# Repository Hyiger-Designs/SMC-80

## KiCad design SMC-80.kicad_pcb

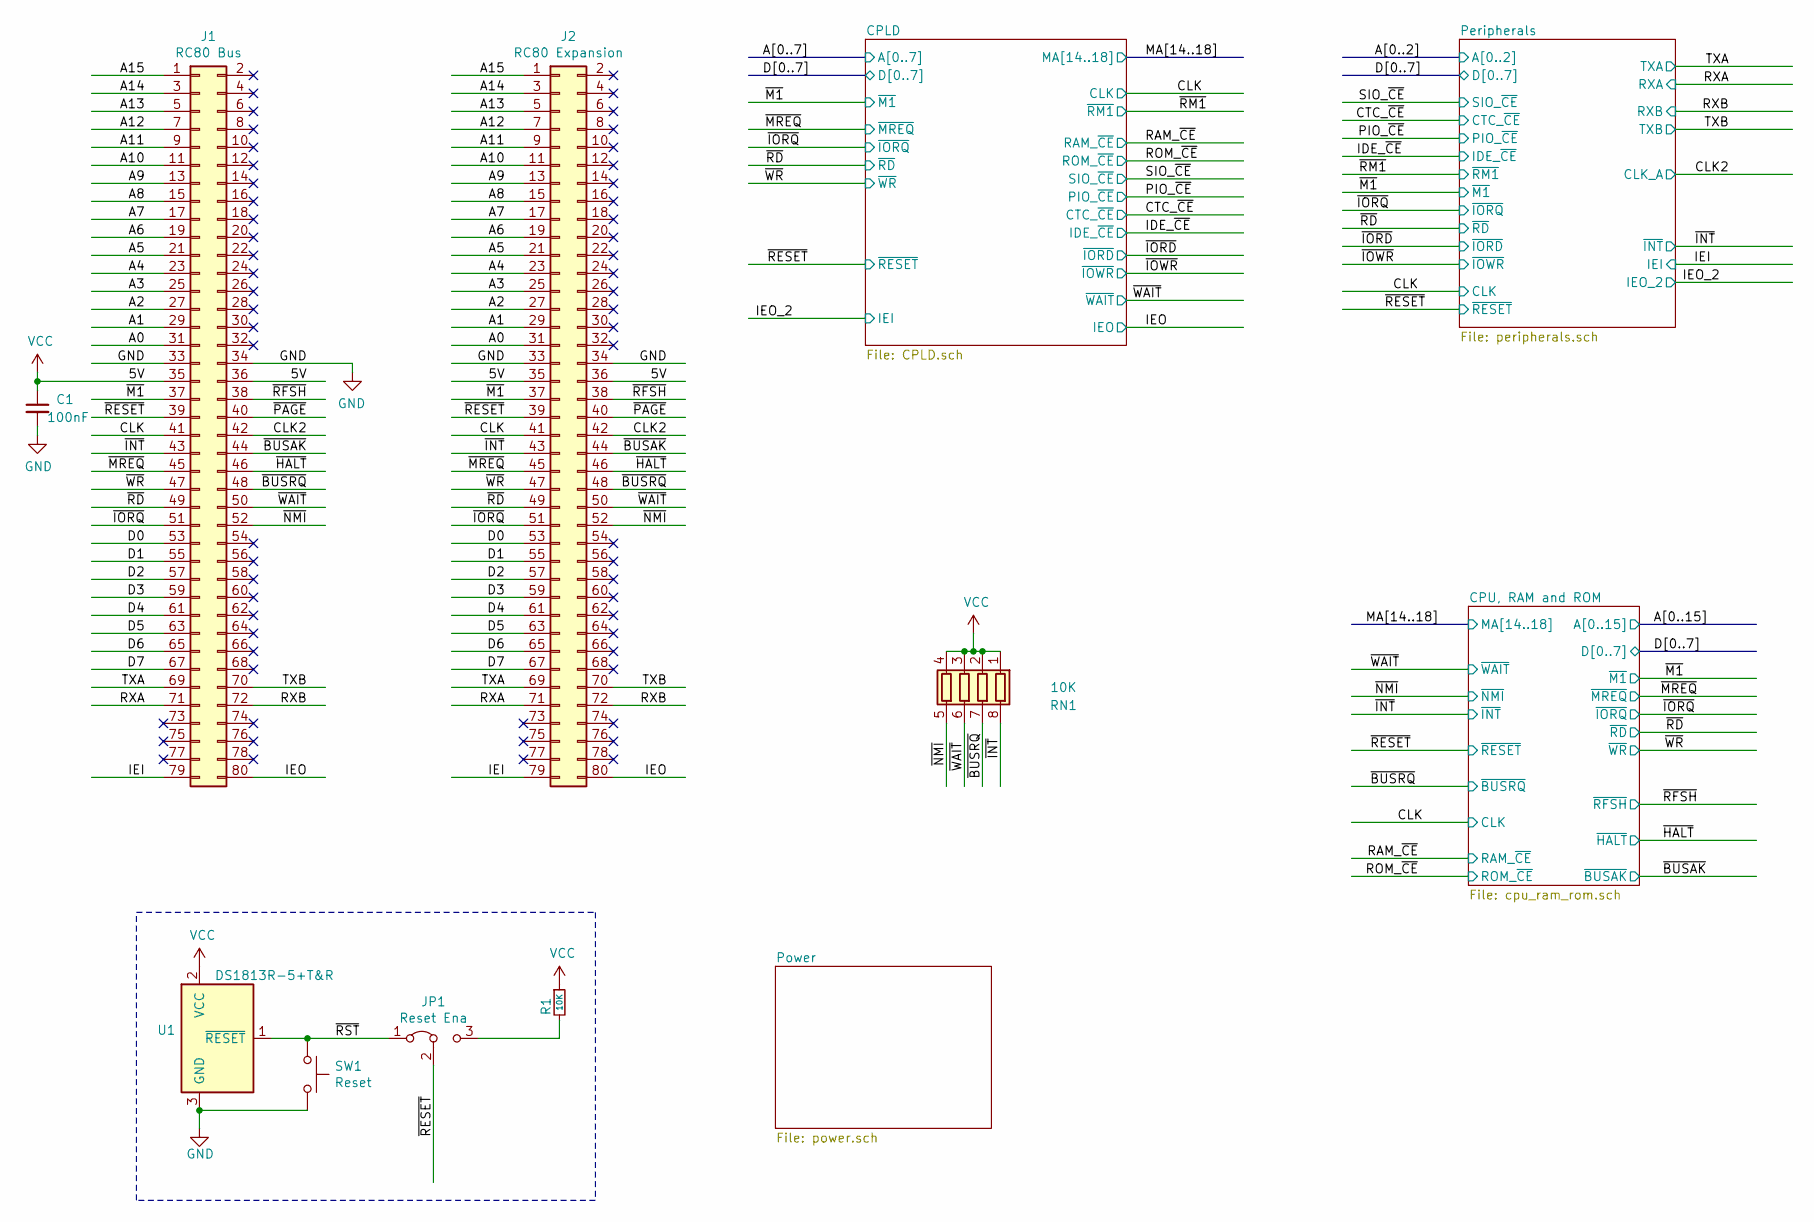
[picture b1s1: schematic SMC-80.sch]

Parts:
C1: 100nF; C_0603_1608Metric_Pad1.05x0.95mm_HandSolder; MPN C0805C105K4RACTU
J1: RC80 Bus; PinSocket_2x40_P2.54mm_Vertical
J2: RC80 Expansion; PinSocket_2x40_P2.54mm_Horizontal
JP1: Reset Ena; PinHeader_1x03_P2.54mm_Vertical
R1: 10K; R_0603_1608Metric_Pad1.05x0.95mm_HandSolder
RN1: 10K; R_Cat16-4
SW1: Reset; SW_SPST_FSMSM
U1: DS1813R-5+T&R; SOT-23

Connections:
/A0: J1.31, J2.31; also elsewhere on the board
/A1: J1.29, J2.29; also elsewhere on the board
/A2: J1.27, J2.27; also elsewhere on the board
/A3: J1.25, J2.25; also elsewhere on the board
/A4: J1.23, J2.23; also elsewhere on the board
/A5: J1.21, J2.21; also elsewhere on the board
/A6: J1.19, J2.19; also elsewhere on the board
/A7: J1.17, J2.17; also elsewhere on the board
/A8: J1.15, J2.15; also elsewhere on the board
/A9: J1.13, J2.13; also elsewhere on the board
/A10: J1.11, J2.11; also elsewhere on the board
/A11: J1.9, J2.9; also elsewhere on the board
/A12: J1.7, J2.7; also elsewhere on the board
/A13: J1.5, J2.5; also elsewhere on the board
/A14: J1.3, J2.3; also elsewhere on the board
/A15: J1.1, J2.1; also elsewhere on the board
/CLK: J1.41, J2.41; also elsewhere on the board
/CLK2: J1.42, J2.42; also elsewhere on the board
/D0: J1.53, J2.53; also elsewhere on the board
/D1: J1.55, J2.55; also elsewhere on the board
/D2: J1.57, J2.57; also elsewhere on the board
/D3: J1.59, J2.59; also elsewhere on the board
/D4: J1.61, J2.61; also elsewhere on the board
/D5: J1.63, J2.63; also elsewhere on the board
/D6: J1.65, J2.65; also elsewhere on the board
/D7: J1.67, J2.67; also elsewhere on the board
/IEI: J1.79, J2.79; also elsewhere on the board
/IEO: J1.80, J2.80; also elsewhere on the board
/RXA: J1.71, J2.71; also elsewhere on the board
/RXB: J1.72, J2.72; also elsewhere on the board
/TXA: J1.69, J2.69; also elsewhere on the board
/TXB: J1.70, J2.70; also elsewhere on the board
/~BUSAK: J1.44, J2.44; also elsewhere on the board
/~BUSRQ: J1.48, J2.48, RN1.7 (R2.2); also elsewhere on the board
/~HALT: J1.46, J2.46; also elsewhere on the board
/~INT: J1.43, J2.43, RN1.8 (R1.2); also elsewhere on the board
/~IORQ: J1.51, J2.51; also elsewhere on the board
/~M1: J1.37, J2.37; also elsewhere on the board
/~MREQ: J1.45, J2.45; also elsewhere on the board
/~NMI: J1.52, J2.52, RN1.5 (R4.2); also elsewhere on the board
/~PAGE: J1.40, J2.40
/~RD: J1.49, J2.49; also elsewhere on the board
/~RESET: J1.39, J2.39, JP1.2 (C); also elsewhere on the board
/~RFSH: J1.38, J2.38; also elsewhere on the board
/~RST: JP1.1 (A), SW1.1, U1.1 (~RESET~)
/~WAIT: J1.50, J2.50, RN1.6 (R3.2); also elsewhere on the board
/~WR: J1.47, J2.47; also elsewhere on the board
GND: C1.2, J1.33, J1.34, J2.33, J2.34, SW1.2, U1.3 (GND); also elsewhere on the board
unnamed: JP1.3 (B), R1.2
VCC: C1.1, J1.35, J1.36, J2.35, J2.36, R1.1, RN1.1 (R1.1), RN1.2 (R2.1), RN1.3 (R3.1), RN1.4 (R4.1), U1.2 (VCC); also elsewhere on the board

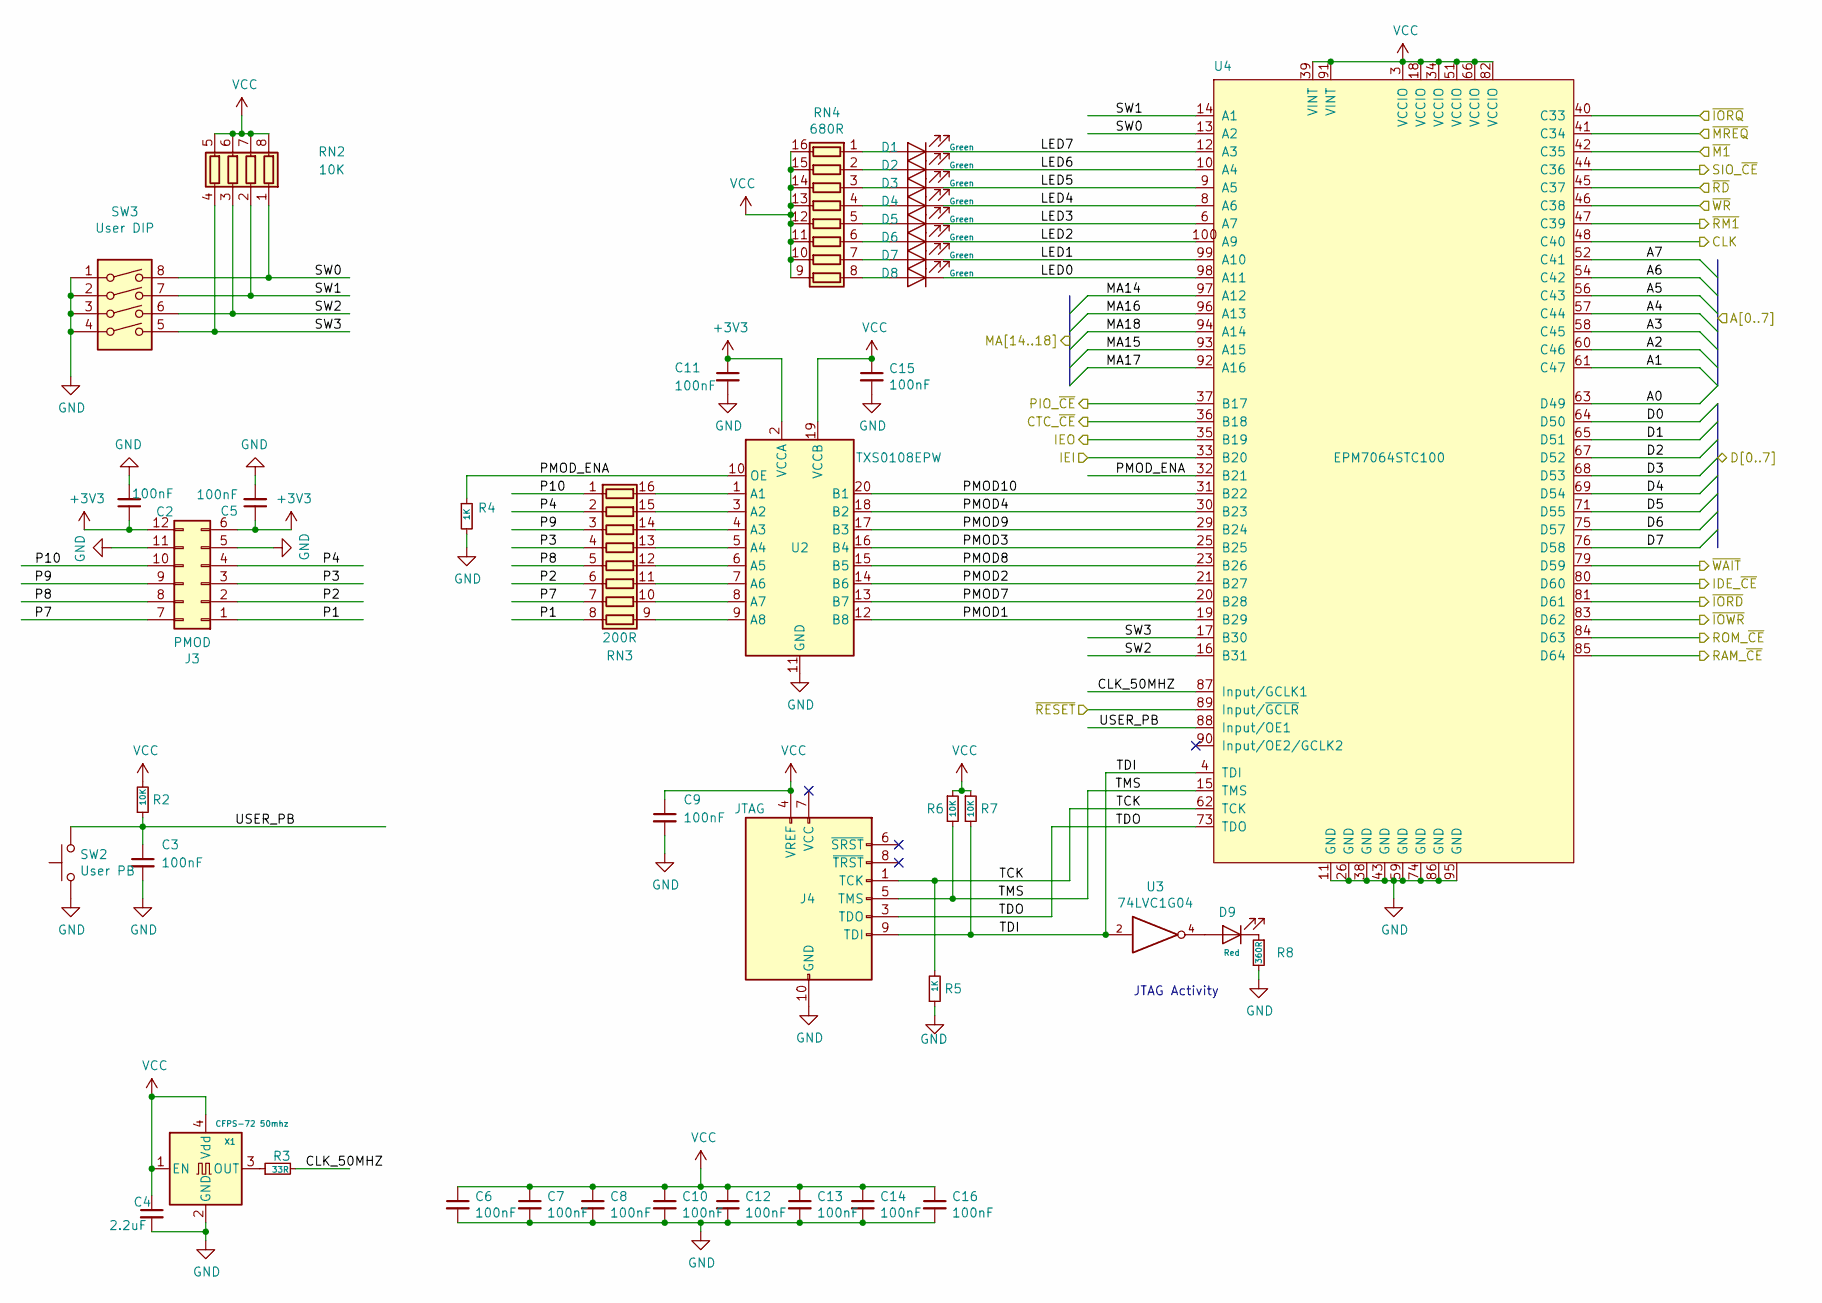
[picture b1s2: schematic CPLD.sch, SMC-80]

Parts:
C2, C5, C6, C7, C8, C10, C11, C12, C13, C14, C15, C16: 100nF; C_0603_1608Metric_Pad1.05x0.95mm_HandSolder
C3, C9: 100nF; C_0603_1608Metric_Pad1.05x0.95mm_HandSolder; MPN JMK107B7474KA-T
C4: 2.2uF; C_0603_1608Metric_Pad1.05x0.95mm_HandSolder; MPN JMK107B7474KA-T
D1, D2, D3, D4, D5, D6, D7, D8: Green; LED_0603_1608Metric_Pad1.05x0.95mm_HandSolder
D9: Red; LED_0603_1608Metric_Pad1.05x0.95mm_HandSolder
J3: PMOD; PinSocket_2x06_P2.54mm_Horizontal_Top_Bottom
J4: JTAG; Multicomp_MC9A12-1034_2x05_P2.54mm_Vertical
R2, R6, R7: 10K; R_0603_1608Metric_Pad1.05x0.95mm_HandSolder
R3: 33R; R_0603_1608Metric_Pad1.05x0.95mm_HandSolder
R4, R5: 1K; R_0603_1608Metric_Pad1.05x0.95mm_HandSolder
R8: 360R; R_0603_1608Metric_Pad1.05x0.95mm_HandSolder
RN2: 10K; R_Cat16-4
RN3: 200R; R_Cat16-8
RN4: 680R; R_Cat16-8
SW2: User PB; SW_SPST_FSMSM
SW3: User DIP; SW_DIP_SPSTx04_Slide_6.7x11.72mm_W8.61mm_P2.54mm_LowProfile
U2: TXS0108EPW; TSSOP-20_4.4x6.5mm_P0.65mm
U3: 74LVC1G04; TSOP-5_1.65x3.05mm_P0.95mm
U4: EPM7064STC100; TQFP-100_14x14mm_P0.5mm
X1: CFPS-72 50mhz; Oscillator_SMD_SeikoEpson_SG8002CA-4Pin_7.0x5.0mm_HandSolde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

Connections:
+3V3: C2.1, C5.1, C11.1, J3.6, J3.12, U2.2 (VCCA); also elsewhere on the board
/A0: U4.63 (D49); also elsewhere on the board
/A1: U4.61 (C47); also elsewhere on the board
/A2: U4.60 (C46); also elsewhere on the board
/A3: U4.58 (C45); also elsewhere on the board
/A4: U4.57 (C44); also elsewhere on the board
/A5: U4.56 (C43); also elsewhere on the board
/A6: U4.54 (C42); also elsewhere on the board
/A7: U4.52 (C41); also elsewhere on the board
/CLK: U4.48 (C40); also elsewhere on the board
/CPLD/CLK_50MHZ: R3.2, U4.87 (Input/GCLK1)
/CPLD/LED0: D8.1 (K), U4.98 (A11)
/CPLD/LED1: D7.1 (K), U4.99 (A10)
/CPLD/LED2: D6.1 (K), U4.100 (A9)
/CPLD/LED3: D5.1 (K), U4.6 (A7)
/CPLD/LED4: D4.1 (K), U4.8 (A6)
/CPLD/LED5: D3.1 (K), U4.9 (A5)
/CPLD/LED6: D2.1 (K), U4.10 (A4)
/CPLD/LED7: D1.1 (K), U4.12 (A3)
/CPLD/MA14: U4.97 (A12); also elsewhere on the board
/CPLD/MA15: U4.93 (A15); also elsewhere on the board
/CPLD/MA16: U4.96 (A13); also elsewhere on the board
/CPLD/MA17: U4.92 (A16); also elsewhere on the board
/CPLD/MA18: U4.94 (A14); also elsewhere on the board
/CPLD/P1: J3.1, RN3.8 (R8.1)
/CPLD/P2: J3.2, RN3.6 (R6.1)
/CPLD/P3: J3.3, RN3.4 (R4.1)
/CPLD/P4: J3.4, RN3.2 (R2.1)
/CPLD/P7: J3.7, RN3.7 (R7.1)
/CPLD/P8: J3.8, RN3.5 (R5.1)
/CPLD/P9: J3.9, RN3.3 (R3.1)
/CPLD/P10: J3.10, RN3.1 (R1.1)
/CPLD/PMOD1: U2.12 (B8), U4.19 (B29)
/CPLD/PMOD2: U2.14 (B6), U4.21 (B27)
/CPLD/PMOD3: U2.16 (B4), U4.25 (B25)
/CPLD/PMOD4: U2.18 (B2), U4.30 (B23)
/CPLD/PMOD7: U2.13 (B7), U4.20 (B28)
/CPLD/PMOD8: U2.15 (B5), U4.23 (B26)
/CPLD/PMOD9: U2.17 (B3), U4.29 (B24)
/CPLD/PMOD10: U2.20 (B1), U4.31 (B22)
/CPLD/PMOD_ENA: R4.1, U2.10 (OE), U4.32 (B21)
/CPLD/SW0: RN2.1 (R1.1), SW3.8, U4.13 (A2)
/CPLD/SW1: RN2.2 (R2.1), SW3.7, U4.14 (A1)
/CPLD/SW2: RN2.3 (R3.1), SW3.6, U4.16 (B31)
/CPLD/SW3: RN2.4 (R4.1), SW3.5, U4.17 (B30)
/CPLD/TCK: J4.1 (TCK), R5.2, U4.62 (TCK)
/CPLD/TDI: J4.9 (TDI), R7.2, U3.2, U4.4 (TDI)
/CPLD/TDO: J4.3 (TDO), U4.73 (TDO)
/CPLD/TMS: J4.5 (TMS), R6.2, U4.15 (TMS)
/CPLD/USER_PB: C3.1, R2.1, SW2.2, U4.88 (Input/OE1)
/CTC_~CE: U4.36 (B18); also elsewhere on the board
/D0: U4.64 (D50); also elsewhere on the board
/D1: U4.65 (D51); also elsewhere on the board
/D2: U4.67 (D52); also elsewhere on the board
/D3: U4.68 (D53); also elsewhere on the board
/D4: U4.69 (D54); also elsewhere on the board
/D5: U4.71 (D55); also elsewhere on the board
/D6: U4.75 (D57); also elsewhere on the board
/D7: U4.76 (D58); also elsewhere on the board
/IDE_~CE~: U4.80 (D60); also elsewhere on the board
/IEO: U4.35 (B19); also elsewhere on the board
/IEO_2: U4.33 (B20); also elsewhere on the board
/PIO_~CE: U4.37 (B17); also elsewhere on the board
/RAM_~CE: U4.85 (D64); also elsewhere on the board
/ROM_~CE: U4.84 (D63); also elsewhere on the board
/SIO_~CE: U4.44 (C36); also elsewhere on the board
/~IORD: U4.81 (D61); also elsewhere on the board
/~IORQ: U4.40 (C33); also elsewhere on the board
/~IOWR: U4.83 (D62); also elsewhere on the board
/~M1: U4.42 (C35); also elsewhere on the board
/~MREQ: U4.41 (C34); also elsewhere on the board
/~RD: U4.45 (C37); also elsewhere on the board
/~RESET: U4.89 (Input/~GCLR); also elsewhere on the board
/~RM1: U4.47 (C39); also elsewhere on the board
/~WAIT: U4.79 (D59); also elsewhere on the board
/~WR: U4.46 (C38); also elsewhere on the board
GND: C2.2, C3.2, C4.2, C5.2, C6.2, C7.2, C8.2, C9.2, C10.2, C11.2, C12.2, C13.2, C14.2, C15.2, C16.2, J3.5, J3.11, J4.2 (GND), J4.10 (GND), R4.2, R5.1, R8.2, SW2.1, SW3.1, SW3.2, SW3.3, SW3.4, U2.11 (GND), U3.3 (GND), U4.11 (GND), U4.26 (GND), U4.38 (GND), U4.43 (GND), U4.59 (GND), U4.74 (GND), U4.86 (GND), U4.95 (GND), X1.2 (GND); also elsewhere on the board
unnamed: D1.2 (A), RN4.1 (R1.1)
unnamed: D2.2 (A), RN4.2 (R2.1)
unnamed: D3.2 (A), RN4.3 (R3.1)
unnamed: D4.2 (A), RN4.4 (R4.1)
unnamed: D5.2 (A), RN4.5 (R5.1)
unnamed: D6.2 (A), RN4.6 (R6.1)
unnamed: D7.2 (A), RN4.7 (R7.1)
unnamed: D8.2 (A), RN4.8 (R8.1)
unnamed: D9.1 (K), R8.1
unnamed: D9.2 (A), U3.4
unnamed: R3.1, X1.3 (OUT)
unnamed: RN3.9 (R8.2), U2.9 (A8)
unnamed: RN3.10 (R7.2), U2.8 (A7)
unnamed: RN3.11 (R6.2), U2.7 (A6)
unnamed: RN3.12 (R5.2), U2.6 (A5)
unnamed: RN3.13 (R4.2), U2.5 (A4)
unnamed: RN3.14 (R3.2), U2.4 (A3)
unnamed: RN3.15 (R2.2), U2.3 (A2)
unnamed: RN3.16 (R1.2), U2.1 (A1)
VCC: C4.1, C6.1, C7.1, C8.1, C9.1, C10.1, C12.1, C13.1, C14.1, C15.1, C16.1, J4.4 (VREF), R2.2, R6.1, R7.1, RN2.5 (R4.2), RN2.6 (R3.2), RN2.7 (R2.2), RN2.8 (R1.2), RN4.9 (R8.2), RN4.10 (R7.2), RN4.11 (R6.2), RN4.12 (R5.2), RN4.13 (R4.2), RN4.14 (R3.2), RN4.15 (R2.2), RN4.16 (R1.2), U2.19 (VCCB), U3.5 (VCC), U4.3 (VCCIO), U4.18 (VCCIO), U4.34 (VCCIO), U4.39 (VINT), U4.51 (VCCIO), U4.66 (VCCIO), U4.82 (VCCIO), U4.91 (VINT), X1.1 (EN), X1.4 (Vdd); also elsewhere on the board

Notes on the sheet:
JTAG Activity

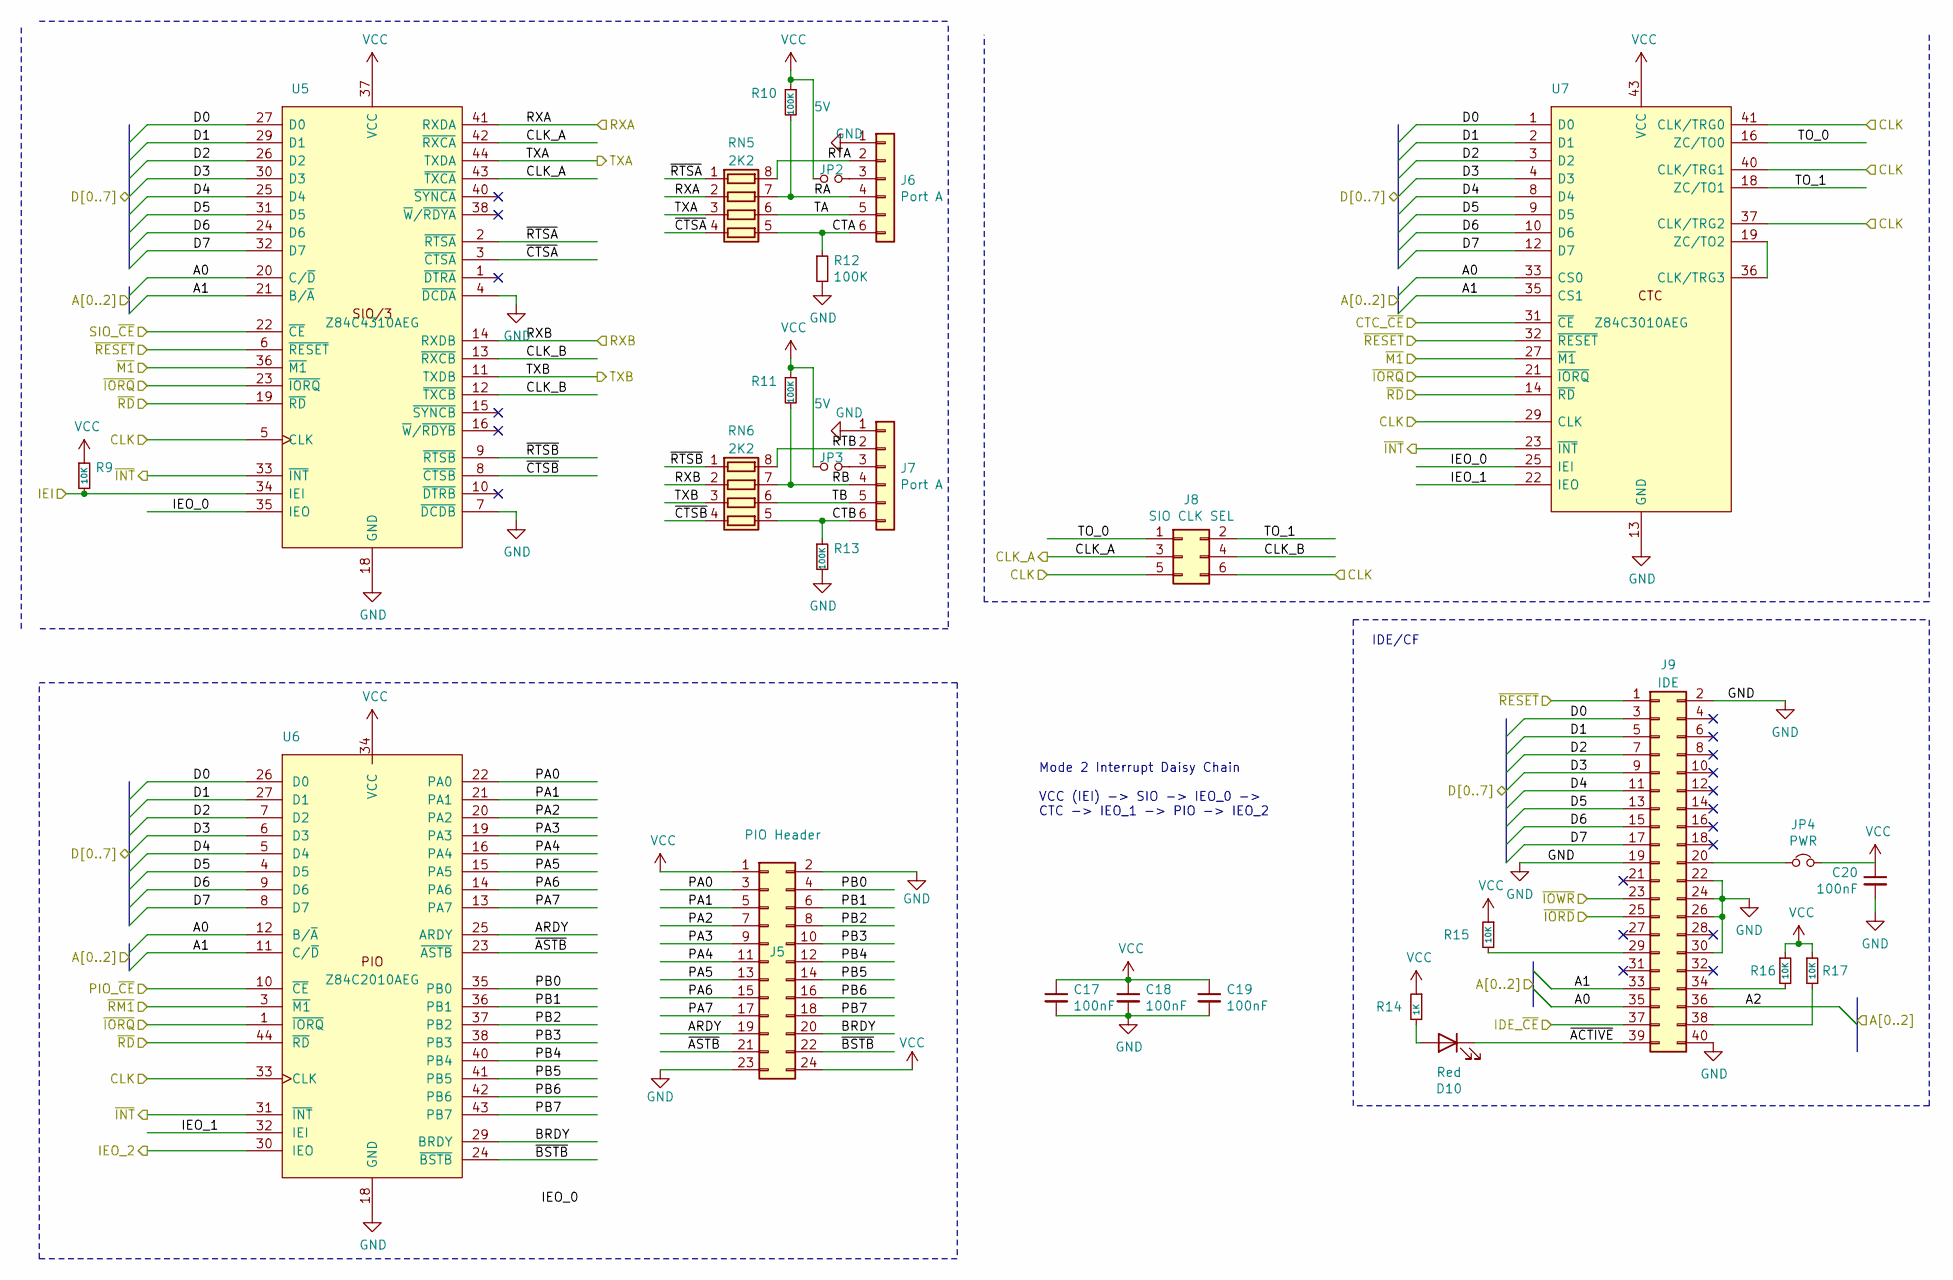
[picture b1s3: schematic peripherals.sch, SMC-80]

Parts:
C17, C18, C19, C20: 100nF; C_0603_1608Metric_Pad1.05x0.95mm_HandSolder; MPN JMK107B7474KA-T
D10: Red; LED_0603_1608Metric_Pad1.05x0.95mm_HandSolder
J5: PIO Header; PinHeader_2x12_P2.54mm_Horizontal
J6, J7: Port A; PinHeader_1x06_P2.54mm_Horizontal
J8: SIO CLK SEL; PinHeader_2x03_P2.54mm_Vertical
J9: IDE; PinHeader_2x20_P2.54mm_Horizontal
JP2, JP3: 5V; PinHeader_1x02_P2.54mm_Vertical
JP4: PWR; PinHeader_1x02_P2.54mm_Vertical
R9, R15, R16, R17: 10K; R_0603_1608Metric_Pad1.05x0.95mm_HandSolder
R10, R11, R12, R13: 100K; R_0603_1608Metric_Pad1.05x0.95mm_HandSolder
R14: 1K; R_0603_1608Metric_Pad1.05x0.95mm_HandSolder
RN5, RN6: 2K2; R_Cat16-4
U5: Z84C4310AEG; LQFP-44_10x10mm_P0.8mm; Manufacturer_Part_Number Z84C4310AEG
U6: Z84C2010AEG; LQFP-44_10x10mm_P0.8mm; Manufacturer_Part_Number Z84C2010AEG
U7: Z84C3010AEG; LQFP-44_10x10mm_P0.8mm; Manufacturer_Part_Number Z84C4310AEG

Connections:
/A0: J9.35, U5.20 (C/~D), U6.12 (B/~A), U7.33 (CS0); also elsewhere on the board
/A1: J9.33, U5.21 (B/~A), U6.11 (C/~D), U7.35 (CS1); also elsewhere on the board
/A2: J9.36; also elsewhere on the board
/CLK: J8.5, J8.6, U5.5 (CLK), U6.33 (CLK), U7.29 (CLK), U7.37 (CLK/TRG2), U7.40 (CLK/TRG1), U7.41 (CLK/TRG0); also elsewhere on the board
/CLK2: J8.3, U5.42 (~RXCA), U5.43 (~TXCA); also elsewhere on the board
/CTC_~CE: U7.31 (~CE); also elsewhere on the board
/D0: J9.3, U5.27 (D0), U6.26 (D0), U7.1 (D0); also elsewhere on the board
/D1: J9.5, U5.29 (D1), U6.27 (D1), U7.2 (D1); also elsewhere on the board
/D2: J9.7, U5.26 (D2), U6.7 (D2), U7.3 (D2); also elsewhere on the board
/D3: J9.9, U5.30 (D3), U6.6 (D3), U7.4 (D3); also elsewhere on the board
/D4: J9.11, U5.25 (D4), U6.5 (D4), U7.8 (D4); also elsewhere on the board
/D5: J9.13, U5.31 (D5), U6.4 (D5), U7.9 (D5); also elsewhere on the board
/D6: J9.15, U5.24 (D6), U6.9 (D6), U7.10 (D6); also elsewhere on the board
/D7: J9.17, U5.32 (D7), U6.8 (D7), U7.12 (D7); also elsewhere on the board
/IDE_~CE~: J9.37; also elsewhere on the board
/IEI: R9.2, U5.34 (IEI); also elsewhere on the board
/IEO_2: U6.30 (IEO); also elsewhere on the board
/PIO_~CE: U6.10 (~CE); also elsewhere on the board
/Peripherals/ARDY: J5.19, U6.25 (ARDY)
/Peripherals/BRDY: J5.20, U6.29 (BRDY)
/Peripherals/CLK_B: J8.4, U5.12 (~TXCB), U5.13 (~RXCB)
/Peripherals/CTA: J6.6, R12.1, RN5.5 (R4.2)
/Peripherals/CTB: J7.6, R13.1, RN6.5 (R4.2)
/Peripherals/IEO_0: U5.35 (IEO), U7.25 (IEI)
/Peripherals/IEO_1: U6.32 (IEI), U7.22 (IEO)
/Peripherals/PA0: J5.3, U6.22 (PA0)
/Peripherals/PA1: J5.5, U6.21 (PA1)
/Peripherals/PA2: J5.7, U6.20 (PA2)
/Peripherals/PA3: J5.9, U6.19 (PA3)
/Peripherals/PA4: J5.11, U6.16 (PA4)
/Peripherals/PA5: J5.13, U6.15 (PA5)
/Peripherals/PA6: J5.15, U6.14 (PA6)
/Peripherals/PA7: J5.17, U6.13 (PA7)
/Peripherals/PB0: J5.4, U6.35 (PB0)
/Peripherals/PB1: J5.6, U6.36 (PB1)
/Peripherals/PB2: J5.8, U6.37 (PB2)
/Peripherals/PB3: J5.10, U6.38 (PB3)
/Peripherals/PB4: J5.12, U6.40 (PB4)
/Peripherals/PB5: J5.14, U6.41 (PB5)
/Peripherals/PB6: J5.16, U6.42 (PB6)
/Peripherals/PB7: J5.18, U6.43 (PB7)
/Peripherals/RA: J6.4, R10.2, RN5.7 (R2.2)
/Peripherals/RB: J7.4, R11.2, RN6.7 (R2.2)
/Peripherals/RTA: J6.2, RN5.8 (R1.2)
/Peripherals/RTB: J7.2, RN6.8 (R1.2)
/Peripherals/TA: J6.5, RN5.6 (R3.2)
/Peripherals/TB: J7.5, RN6.6 (R3.2)
/Peripherals/TO_0: J8.1, U7.16 (ZC/TO0)
/Peripherals/TO_1: J8.2, U7.18 (ZC/TO1)
/Peripherals/~ACTIVE: D10.1 (K), J9.39
/Peripherals/~ASTB: J5.21, U6.23 (~ASTB)
/Peripherals/~BSTB: J5.22, U6.24 (~BSTB)
/Peripherals/~CTSA: RN5.4 (R4.1), U5.3 (~CTSA)
/Peripherals/~CTSB: RN6.4 (R4.1), U5.8 (~CTSB)
/Peripherals/~RTSA: RN5.1 (R1.1), U5.2 (~RTSA)
/Peripherals/~RTSB: RN6.1 (R1.1), U5.9 (~RTSB)
/RXA: RN5.2 (R2.1), U5.41 (RXDA); also elsewhere on the board
/RXB: RN6.2 (R2.1), U5.14 (RXDB); also elsewhere on the board
/SIO_~CE: U5.22 (~CE); also elsewhere on the board
/TXA: RN5.3 (R3.1), U5.44 (TXDA); also elsewhere on the board
/TXB: RN6.3 (R3.1), U5.11 (TXDB); also elsewhere on the board
/~INT: U5.33 (~INT), U6.31 (~INT), U7.23 (~INT); also elsewhere on the board
/~IORD: J9.25; also elsewhere on the board
/~IORQ: U5.23 (~IORQ), U6.1 (~IORQ), U7.21 (~IORQ); also elsewhere on the board
/~IOWR: J9.23; also elsewhere on the board
/~M1: U5.36 (~M1), U7.27 (~M1); also elsewhere on the board
/~RD: U5.19 (~RD), U6.44 (~RD), U7.14 (~RD); also elsewhere on the board
/~RESET: J9.1, U5.6 (~RESET), U7.32 (~RESET); also elsewhere on the board
/~RM1: U6.3 (~M1); also elsewhere on the board
GND: C17.2, C18.2, C19.2, C20.2, J5.2, J5.23, J6.1, J7.1, J9.2, J9.19, J9.22, J9.24, J9.26, J9.30, J9.40, R12.2, R13.2, U5.4 (~DCDA), U5.7 (~DCDB), U5.18 (GND), U6.18 (GND), U7.13 (GND); also elsewhere on the board
unnamed: D10.2 (A), R14.2
unnamed: J6.3, JP2.2
unnamed: J7.3, JP3.2
unnamed: J9.20, JP4.1
unnamed: J9.29, R15.2
unnamed: J9.34, R16.2
unnamed: J9.38, R17.2
unnamed: U7.19 (ZC/TO2), U7.36 (CLK/TRG3)
VCC: C17.1, C18.1, C19.1, C20.1, J5.1, J5.24, JP2.1, JP3.1, JP4.2, R9.1, R10.1, R11.1, R14.1, R15.1, R16.1, R17.1, U5.37 (VCC), U6.34 (VCC), U7.43 (VCC); also elsewhere on the board

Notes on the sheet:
IDE/CF
Mode 2 Interrupt Daisy Chain VCC (IEI) -> SIO -> IEO_0 -> CTC -> IEO_1 -> PIO -> IEO_2

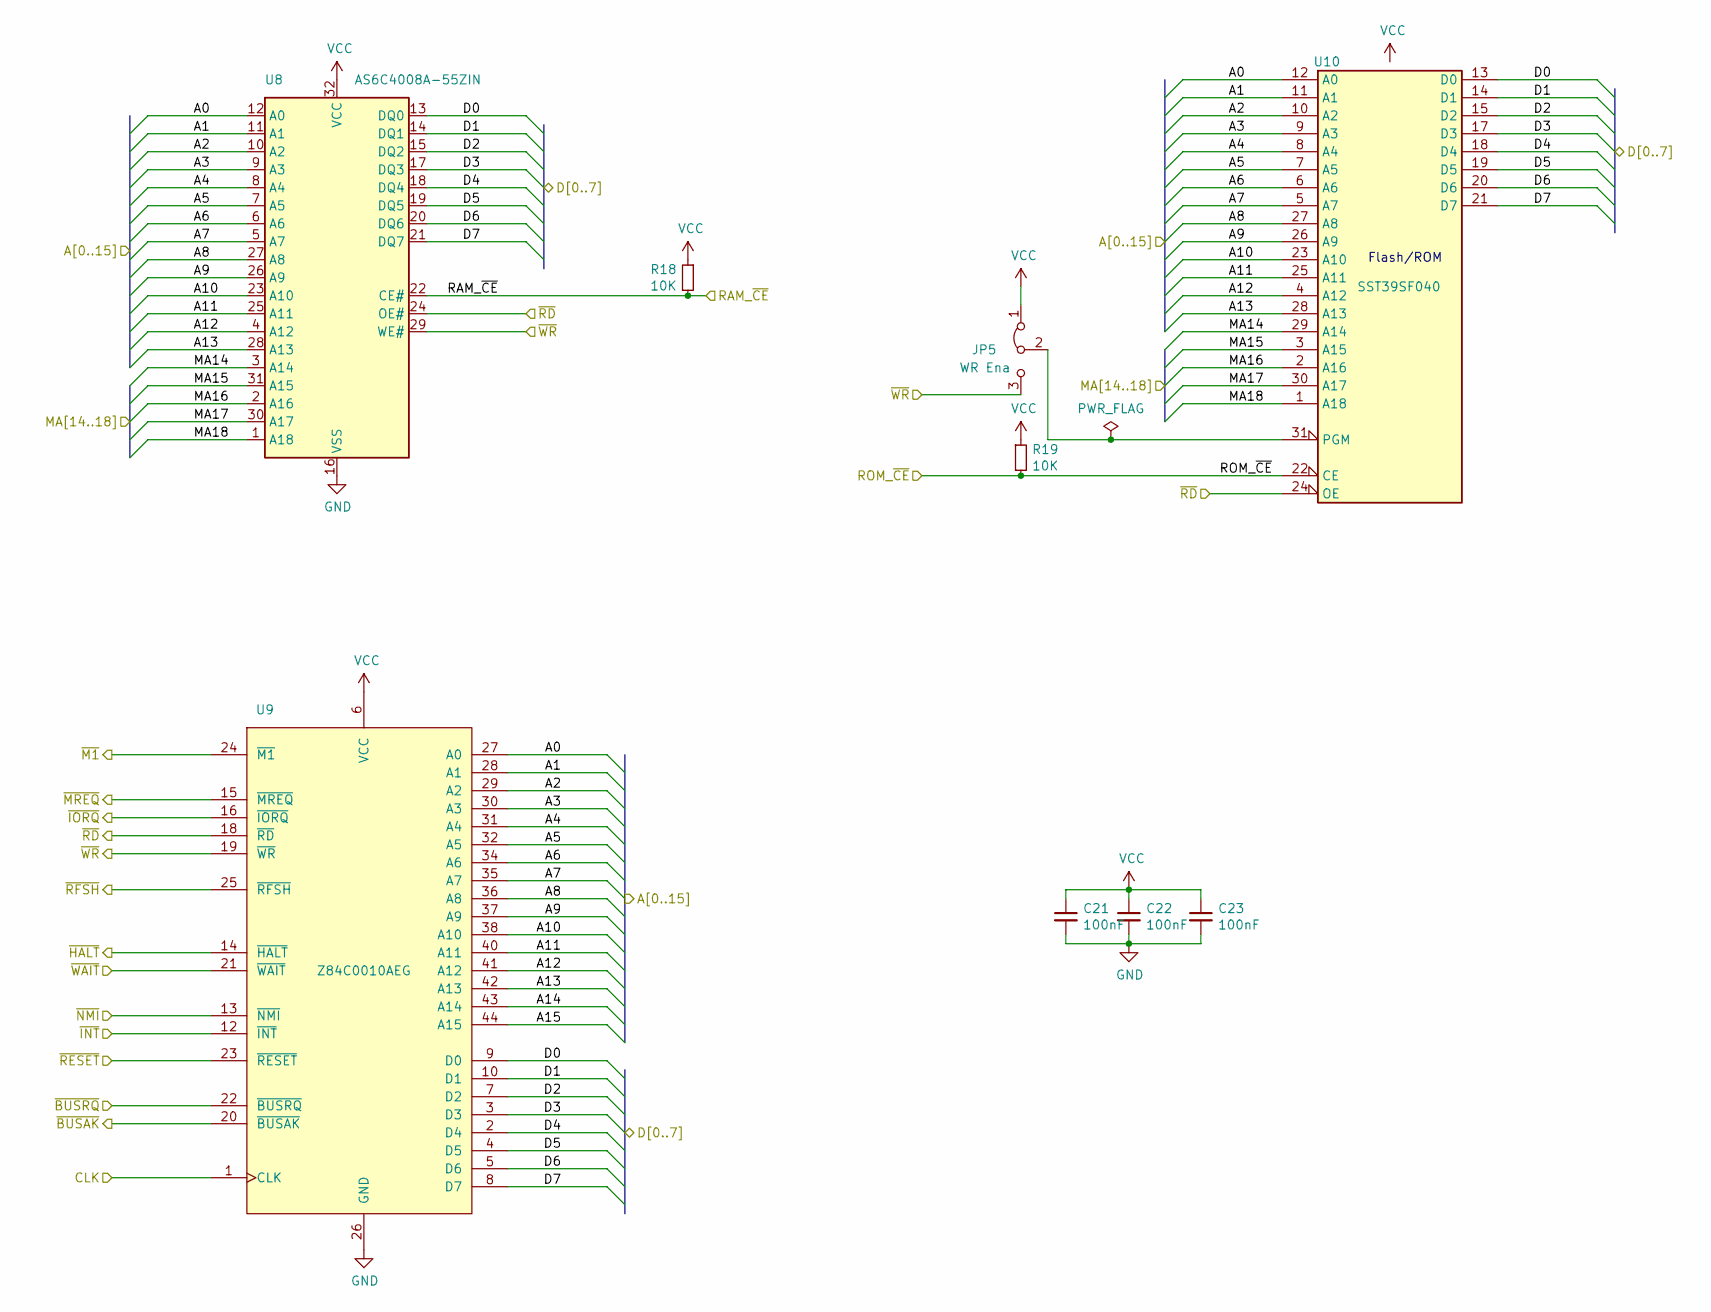
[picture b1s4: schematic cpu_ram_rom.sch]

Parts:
C21, C22, C23: 100nF; C_0603_1608Metric_Pad1.05x0.95mm_HandSolder
JP5: WR Ena; PinHeader_1x03_P2.54mm_Vertical
R18, R19: 10K; R_0603_1608Metric_Pad1.05x0.95mm_HandSolder
U8: AS6C4008A-55ZIN; TSOP-II-32_21.0x10.2mm_P1.27mm
U9: Z84C0010AEG; LQFP-44_10x10mm_P0.8mm; Manufacturer_Part_Number Z84C0010AEG
U10: SST39SF040; PLCC-32_11.4x14.0mm_P1.27mm

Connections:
/A0: U8.12 (A0), U9.27 (A0), U10.12 (A0); also elsewhere on the board
/A1: U8.11 (A1), U9.28 (A1), U10.11 (A1); also elsewhere on the board
/A2: U8.10 (A2), U9.29 (A2), U10.10 (A2); also elsewhere on the board
/A3: U8.9 (A3), U9.30 (A3), U10.9 (A3); also elsewhere on the board
/A4: U8.8 (A4), U9.31 (A4), U10.8 (A4); also elsewhere on the board
/A5: U8.7 (A5), U9.32 (A5), U10.7 (A5); also elsewhere on the board
/A6: U8.6 (A6), U9.34 (A6), U10.6 (A6); also elsewhere on the board
/A7: U8.5 (A7), U9.35 (A7), U10.5 (A7); also elsewhere on the board
/A8: U8.27 (A8), U9.36 (A8), U10.27 (A8); also elsewhere on the board
/A9: U8.26 (A9), U9.37 (A9), U10.26 (A9); also elsewhere on the board
/A10: U8.23 (A10), U9.38 (A10), U10.23 (A10); also elsewhere on the board
/A11: U8.25 (A11), U9.40 (A11), U10.25 (A11); also elsewhere on the board
/A12: U8.4 (A12), U9.41 (A12), U10.4 (A12); also elsewhere on the board
/A13: U8.28 (A13), U9.42 (A13), U10.28 (A13); also elsewhere on the board
/A14: U9.43 (A14); also elsewhere on the board
/A15: U9.44 (A15); also elsewhere on the board
/CLK: U9.1 (CLK); also elsewhere on the board
/CPLD/MA14: U8.3 (A14), U10.29 (A14); also elsewhere on the board
/CPLD/MA15: U8.31 (A15), U10.3 (A15); also elsewhere on the board
/CPLD/MA16: U8.2 (A16), U10.2 (A16); also elsewhere on the board
/CPLD/MA17: U8.30 (A17), U10.30 (A17); also elsewhere on the board
/CPLD/MA18: U8.1 (A18), U10.1 (A18); also elsewhere on the board
/D0: U8.13 (DQ0), U9.9 (D0), U10.13 (D0); also elsewhere on the board
/D1: U8.14 (DQ1), U9.10 (D1), U10.14 (D1); also elsewhere on the board
/D2: U8.15 (DQ2), U9.7 (D2), U10.15 (D2); also elsewhere on the board
/D3: U8.17 (DQ3), U9.3 (D3), U10.17 (D3); also elsewhere on the board
/D4: U8.18 (DQ4), U9.2 (D4), U10.18 (D4); also elsewhere on the board
/D5: U8.19 (DQ5), U9.4 (D5), U10.19 (D5); also elsewhere on the board
/D6: U8.20 (DQ6), U9.5 (D6), U10.20 (D6); also elsewhere on the board
/D7: U8.21 (DQ7), U9.8 (D7), U10.21 (D7); also elsewhere on the board
/RAM_~CE: R18.2, U8.22 (CE#); also elsewhere on the board
/ROM_~CE: R19.2, U10.22 (CE); also elsewhere on the board
/~BUSAK: U9.20 (~BUSAK); also elsewhere on the board
/~BUSRQ: U9.22 (~BUSRQ); also elsewhere on the board
/~HALT: U9.14 (~HALT); also elsewhere on the board
/~INT: U9.12 (~INT); also elsewhere on the board
/~IORQ: U9.16 (~IORQ); also elsewhere on the board
/~M1: U9.24 (~M1); also elsewhere on the board
/~MREQ: U9.15 (~MREQ); also elsewhere on the board
/~NMI: U9.13 (~NMI); also elsewhere on the board
/~RD: U8.24 (OE#), U9.18 (~RD), U10.24 (OE); also elsewhere on the board
/~RESET: U9.23 (~RESET); also elsewhere on the board
/~RFSH: U9.25 (~RFSH); also elsewhere on the board
/~WAIT: U9.21 (~WAIT); also elsewhere on the board
/~WR: JP5.3 (B), U8.29 (WE#), U9.19 (~WR); also elsewhere on the board
GND: C21.2, C22.2, C23.2, U8.16 (VSS), U9.26 (GND), U10.16 (GND); also elsewhere on the board
unnamed: JP5.2 (C), U10.31 (PGM)
VCC: C21.1, C22.1, C23.1, JP5.1 (A), R18.1, R19.1, U8.32 (VCC), U9.6 (VCC), U10.32 (VCC); also elsewhere on the board

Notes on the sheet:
Flash/ROM

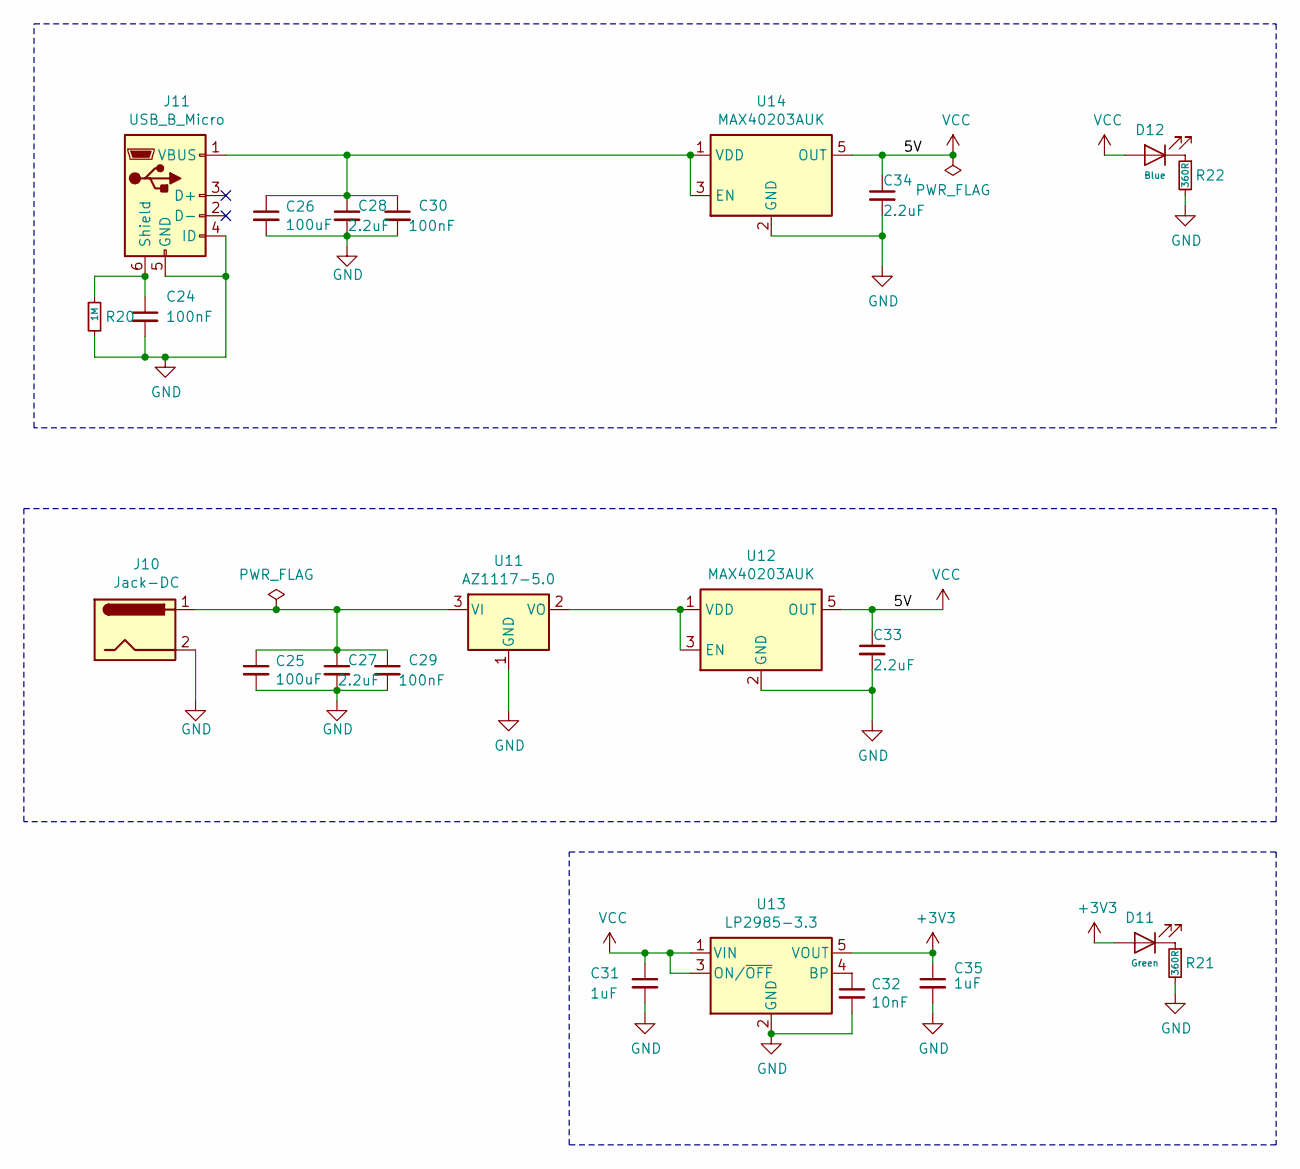
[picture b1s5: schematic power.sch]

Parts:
C24, C29, C30: 100nF; C_0603_1608Metric_Pad1.05x0.95mm_HandSolder; MPN C0805C105K4RACTU
C25, C26: 100uF; C_1206_3216Metric_Pad1.42x1.75mm_HandSolder
C27, C28, C33, C34: 2.2uF; C_0603_1608Metric_Pad1.05x0.95mm_HandSolder; MPN C0805C105K4RACTU
C31, C35: 1uF; C_0603_1608Metric_Pad1.05x0.95mm_HandSolder
C32: 10nF; C_0603_1608Metric_Pad1.05x0.95mm_HandSolder
D11: Green; LED_0603_1608Metric_Pad1.05x0.95mm_HandSolder
D12: Blue; LED_0603_1608Metric_Pad1.05x0.95mm_HandSolder
J10: Jack-DC; BarrelJack_CUI_PJ-063AH_Horizontal
J11: USB_B_Micro; USB_Micro-B_Amphenol_10103594-0001LF_Horizontal; MPN 10103594-0001LF
R20: 1M; R_0603_1608Metric_Pad1.05x0.95mm_HandSolder
R21, R22: 360R; R_0603_1608Metric_Pad1.05x0.95mm_HandSolder
U11: AZ1117-5.0; TO-252-3_TabPin2
U12, U14: MAX40203AUK; SOT-23-5_HandSoldering; MPN MAX40203AUK+T; Mouser PN 700-MAX40203AUK+T
U13: LP2985-3.3; SOT-23-5

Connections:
+3V3: C35.1, D11.2 (A), U13.5 (VOUT); also elsewhere on the board
GND: C24.2, C25.2, C26.2, C27.2, C28.2, C29.2, C30.2, C31.2, C32.2, C33.2, C34.2, C35.2, J10.2, J11.4 (ID), J11.5 (GND), R20.2, R21.2, R22.2, U11.1 (GND), U12.2 (GND), U13.2 (GND), U14.2 (GND); also elsewhere on the board
unnamed: C24.1, J11.6 (Shield), R20.1
unnamed: C25.1, C27.1, C29.1, J10.1, U11.3 (VI)
unnamed: C26.1, C28.1, C30.1, J11.1 (VBUS), U14.1 (VDD), U14.3 (EN)
unnamed: C32.1, U13.4 (BP)
unnamed: D11.1 (K), R21.1
unnamed: D12.1 (K), R22.1
unnamed: U11.2 (VO), U12.1 (VDD), U12.3 (EN)
VCC: C31.1, C33.1, C34.1, D12.2 (A), U12.5 (OUT), U13.1 (VIN), U13.3 (ON/~OFF~), U14.5 (OUT); also elsewhere on the board
